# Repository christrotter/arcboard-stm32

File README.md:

# 2025/11/25 update
Ok, we found the main problem.
The Schottky diode on the main VBUS inbound power leg (just after the main polyfuse) was the problem.  After many hours of troubleshooting, we discovered that it was the thing getting hot.
More digging revealed that it had a 1A max, and after 75C its performance tanked pretty fast.  In practice it could tolerate about 0.5A before overheating got out of hand.
I replaced it with a bodge wire and the overheating problem went away - the board is now just warm with 1.1A going through it - probably some other components are 1A-rated.  I did not anticipate drawing this much current... my bad!
As a side effect of removing the diode, VBUS detection no longer works properly, so that needs to be disabled in code.

The next iteration will be a massive overhaul, so I'm not going to fix the problem.  In theory, we need both a higher quality component, a bigger package, and higher current rating.

# 2025/11/23 update 
I've, unsurprisingly, found some flaws.
Aside from the flaws mentioned (that were fixed), there's something very wrong with the power filter circuit or power trace widths.
Everything works, but it consumes 2x the power it should be consuming, and overwhelms the power traces so that they get rather hot.  I had to reduce brightness quite a bit to keep it at 'warm' levels.  Unfortunately I don't own an infrared camera, so only have temperature sensing by feel, but the area that gets hottest is in the power filter area.  I tried using the solder pad bypass, but no difference.
So, feels like it's a trace problem...?  Or maybe a bad component?  Will update when I figure it out.
If you're only running the Cyboard pcbs, PMW, dpad/paddles, it consumes about 0.25A per side.

# stm32-inator

In the search for better performance, I moved from [RP2040](https://github.com/christrotter/mk19-rp2040) (`125mhz`) to STM32F405 (`168mhz`).  Getting familiar with STM32 also allows me more confidence to move to the H7** chips in future (`550mhz`).

`v1.0 board has been tested - works w. 2 easy bodges & code.  Issues fixed in v1.1 - won't be ordering that, so untested - minor changes, should be fine?`

Many thanks to Drashna, burkfers, GeorgeN, badjeff, and the various people (tzarc) I snaggled stuff from - as always, these projects are a community effort.

## First run production

### issues
While things work, there are some problems...
- both mosfets are incorrectly wired up (maybe bad footprint?), and frankly i don't see a need for them as we're not doing batteries; the original thought was 'full power down', dunno if that's a real need; clipping them off removes the issue, and there are sufficient workarounds
- the DFU circuit cannot tolerate the LCD being plugged in; something? in that circuit prevents the cap from charging up
  - there is something foundational here that I am not equipped to deal with atm; 'works, until 3v3 devices in play'

### discoveries
...and some 'you have to try it to know' discoveries, and secondary pcb issues...
- 8mhz crystal is not the default in QMK -> 12mhz is; can be fixed in a few lines of code, but not ideal
- turns out 10 ffc cables are pretty annoying and i'd have been better served moving to two custom ffc cables
- the ffc connectors are kinda sad to use; need to make some kind of tool? -> kinda points in the direction of hot plate if i want to be choosy about parts
- the horizontal JST-XH fit...barely... i neglected to account for 'space to slide the connector in' and so you need to trim the JST housings to avoid fouling on parts - move away from this design in future, JST-PH?

### wins
...but not all is lost:
- remote usb port works absolutely fine
- DFU circuit is super rad (when it works)
- no awful bodging required this time!
- the diode arrays work
- STM32 cpu/etc all works
- silkscreen looks good
- matrix works
- spi pmw/lcd work

### conclusion
All in all, this is a win, and it'll work for mk20.

# Features
- STM32F405RGTx w. 12mhz crystal
- 128mb external flash via SPI
  - Because I Can™ by drashna®
- FFC connections (mostly), using VIK-footprinted 12-pin 0.5mm pitch connectors
- Rough footprint is 60x60mm
- Designed for remote-mount USB and split-serial ports
- WS2812 signal conversion to 5v
- Two-stage DFU button, on-board for convenience, headers for an external button
  - Press for reset
  - Hold for ~4s to enter DFU mode for flashing
  - `NOTE: when 3v3 devices are connected, the hold-for-dfu stops working :'(`
- Designed for Arcboard-mk20 peripherals
  - 4x dpad outputs (5rows, 1col, LED DI/DO, 5v/gnd)
  - 3x encoders outputs (encoder A/B, 3.3v/gnd)
  - 1x SPI PMW output (usual pins)
  - 1x SPI LCD output (usual pins)
  - 1x 25-pin Cyboard connector (0.3mm FPC connector for [Cyboard](https://www.cyboard.digital/product-page/dactyl-flex-pcbs) connectivity (or via [this](https://github.com/christrotter/mk19-flex-pcb)))
- 2-layer design for simplicity and cost

# Design notes & decisions
## CPU
I had originally wanted to go whole-hog and start with STM32H723 (as mentioned, 550mhz), but there are a lot of Chibios/QMK config bits to set that are not well-documented at present.  As 550mhz is super overkill for a keyboard, it's not a widely used chip - so examples are sparse or non-existent.

Drashna recommended starting with F405 and so who am I to second-guess them.

## Flash
At present (August 2025) QMK cannot support external flash for code execution, but feature work is on-going.  I was advised by Drashna to include the flash chip for future-proofing.  My hope is to use it for icon storage and the like.

Why 128mb?  Because it was a few bucks difference compared to 16mb, and there was no real (evident) reason not to.

## Remote-mount USB/split-serial port
This is mostly a mk20 design thing - I wanted to have the split-serial connector be at an angle, not coming off the back of the board.  When the ports are in the back, it's awkward to figure out which one is main, which one is split.  Drashna pointed out that he's been using [these](https://www.aliexpress.com/item/1005005997783735.html) which have 12cm cables and has no USB issues at all.  After a hiccup with JLC PCBA design review, I had to cancel the order and re-submit, and took the plunge...there was no room for both an on-board port and breakout pins.

  - JLC PCBA charges ~C$6 per usb port (per board...), and I've had soldering issues w. those components before
  - No more fuss with v-cut layer drama and them wanting me to use EasyEDA
  - I don't have a USB-C source, and I'm not selling this, so...whatever...
  - note that the remote-port needs to have 5.1k pull-down resistors on the CC lines to function on a USB-C host port

## Device/peripheral connectivity
I explicitly wanted to move away from JST-XH (or any soldered connector) because of pain issues doing all that soldering.  This board's goal was 'minimize soldering, maximize PCBA-ing'.

Given that I like the [VIK standard](https://github.com/sadekbaroudi/vik), I went with VIK footprints - 12-pin 0.5mm pitch FFC.  Not all of the pinouts are VIK-correct, but at least it keeps things somewhat standardized.

## Breakouts
To save space while also future-proofing, I was advised to include breakouts (thx GeorgeN/burkfers).

- Main USB & Split/serial via 2.54mm 4-pin header (I left room for a horizontal JST-XH socket)
- RGB data output via 2.54mm 3-pin header
- Reset, boot pins via 1.00mm 4-pin header
- 5 spare pins via 1.00mm 2-pin and 3-pin headers
- Debug pins via 1.00mm 4-pin header

## Spare pins
The 5 spare pins were initially going to be used for the matrix, but I cut out some features (RKJXT) and didn't need them.  They are available via headers.

Suggestions I've had:
- audio
- haptic

## Solder pads
There are a number of 'config' settings you can achieve using solder pads.  I had originally thought about using DIP switches or something...but burkfers counseled me to just stick with solder pads.

- Set [handedness](https://docs.qmk.fm/features/split_keyboard#handedness-by-pin)
- Bypass VBUS power safeties (I keep this in because I don't know what a fuse failure would look like)
- "turn on" power to the RGB and LCD mosfets

## PCB design
I decided to stick with a 2-layer stackup because I was already comfortable with using pours and vias to keep the ground plane consistent.  We'll see if that pans out.

It's important to note that if you don't provide for good ground pathing 2-layers is a bad choice.  It's "easier" to do a 4-layer board in that regard.

When ordering, I used the 'rails by JLC' option.

## Dimensions
[The RP2040 board](https://github.com/christrotter/mk19-rp2040) was `~125x75mm`, and burkfers challenged me to make this one more compact.  So a few design iterations in and we got `~60x60mm`... which unfortunately got mangled to `59.5x59.7mm`.  I'm still learning pcb design, and Kicad doesn't make it easy (or I have yet to learn the method) to keep things oriented/placed relative to center.

- 51.55mm hole spacing (square)
- M3 holes
- 59.5x59.7mm actual board size

## Matrix arrangement
I moved away from the SPI register design not because it was broken, but because you are effectively artificially limiting 'speed' with the SPI bus (sort of?).  I'm using `ROW2COL` because the Cyboard pcb's are designed this way.  

I decided to try diode "arrays" ([BAV70S - High-speed switching double diode](https://jlcpcb.com/partdetail/Nexperia-BAV70S115/C455031)) this time to save space.  However, this came with some fairly dramatic trace routing challenges.

- 6 rows
- 10 columns

## QMK
I mention `ROW2COL` and QMK not because ZMK or other won't work, but because it's what I am familiar with.

This board is intended to control half of a split keyboard, so you need two.

# Links
- [Datasheet for STM32F405](https://www.st.com/resource/en/datasheet/dm00037051.pdf)
- [Great article on STM32 DFU circuit](https://acheronproject.com/reset_article_1/reset_article_1/)
- [Great article on USB-C CC lines](https://hackaday.com/2023/01/04/all-about-usb-c-resistors-and-emarkers/)
- [TI pdf on USB-C power](https://www.ti.com/lit/wp/slyy109b/slyy109b.pdf)
- [USB and Type-C demystified](https://www.st.com/content/dam/AME/2019/technology-tour-2019/chicago/presentations/T1S3_Schaumburg_USB-Type-C_G.Gosciniak.pdf)
- [SPI flash on STM32](https://mischianti.org/stm32-add-spi-flash-memory-with-fat-fs/)

# BOM (v1.1)
|Designator                                  |Footprint                              |Quantity|Value               |LCSC Part #|
|--------------------------------------------|---------------------------------------|--------|--------------------|-----------|
|C1, C10, C20                                |0805                                   |3       |4.7uF               |C1779      |
|C11, C12, C14, C17, C18, C19, C5, C7, C8, C9|0402                                   |10      |100nF               |C1525      |
|C13, C15, C27                               |0402                                   |3       |1uF                 |C52923     |
|C2, C4                                      |0402                                   |2       |2.2uF               |C12530     |
|C22                                         |C0603                                  |1       |CL10A106MA8NRNC     |C96446     |
|C3, C6                                      |0402                                   |2       |12p                 |C1547      |
|CYBOARD-MAIN1                               |FPC-SMD_ECT818001569                   |1       |ECT818001569        |C711420    |
|D2                                          |D_SOD-323                              |1       |B5817               |C123899    |
|D4                                          |SOD-123FL_L2.8-W1.8-LS3.7-BI           |1       |SMF5_0CA_C364279    |C364279    |
|D5, D7                                      |SOT-666-6_L1.6-W1.2-P0.50-LS1.6-BL     |2       |USBLC6-2P6_C2827693 |C2827693   |
|F1                                          |F1206                                  |1       |Polyfuse            |C2892424   |
|F3                                          |F1206                                  |1       |MF-NSMF075-2        |C89653     |
|J13, J14, J15, J16, J3, J4, J6, J7, J8      |FFC-SMD_FFC05001-12SBA124W5M           |9       |FFC05001-12SBA124W5M|C2833760   |
|L1                                          |L0805                                  |1       |MPZ2012S101AT000    |C15957     |
|LED-LVL1                                    |SOT-563_L1.6-W1.2-P0.50-LS1.6-BR       |1       |SN74LVC1T45DRL      |C352970    |
|MOSFET1, MOSFET2, MOSFET3                   |SOT-23_L2.9-W1.3-P1.90-LS2.4-BR        |3       |AO3401A             |C15127     |
|R1                                          |0402                                   |1       |0402WGF1004TCE      |C26083     |
|R10                                         |0402                                   |1       |5.1k                |C25905     |
|R11, R12, R16, R2, R3, R7, R8               |0402                                   |7       |10k                 |C25744     |
|R14                                         |0402                                   |1       |0402WGF1000TCE      |C25076     |
|R15                                         |0402                                   |1       |0402WGF1001TCE      |C11702     |
|R6                                          |R0603                                  |1       |0603WAF3303T5E      |C23137     |
|R9                                          |0402                                   |1       |0402WGF1003TCE      |C25741     |
|U1                                          |SOT-23-5                               |1       |XC6210B332MR-G      |C82942     |
|U10                                         |SOD-123F_L2.7-W1.6-LS3.8-RD            |1       |1N4148W_C81598      |C81598     |
|U13, U4                                     |SOT-23-3_L2.9-W1.3-P1.90-LS2.4-BR      |2       |2N7002              |C8545      |
|U14                                         |SOIC-8_L5.3-W5.3-P1.27-LS8.0-BL        |1       |W25Q128JVSIQTR      |C97521     |
|U15                                         |SW-SMD_4P-L5.1-W5.1-P3.70-LS6.5-TL_H1.5|1       |TS-1187A-B-A-B      |C318884    |
|U3                                          |LQFP-64_10x10mm_P0.5mm                 |1       |STM32F405RGTx       |C15742     |
|U5, U6, U7, U8, U9                          |SOT-363-6_L2.0-W1.3-P0.65-LS2.1-BL     |5       |BAV70S,115          |C455031    |
|Y1                                          |CRYSTAL-SMD_4P-L3.2-W2.5-BL-1          |1       |Crystal_GND24       |C9002      |

# Layout

# PCB overview

# Schematic
`NOTE: I didn't update the screenshots, sorry.  See the kicad files for the fixed mosfets.`

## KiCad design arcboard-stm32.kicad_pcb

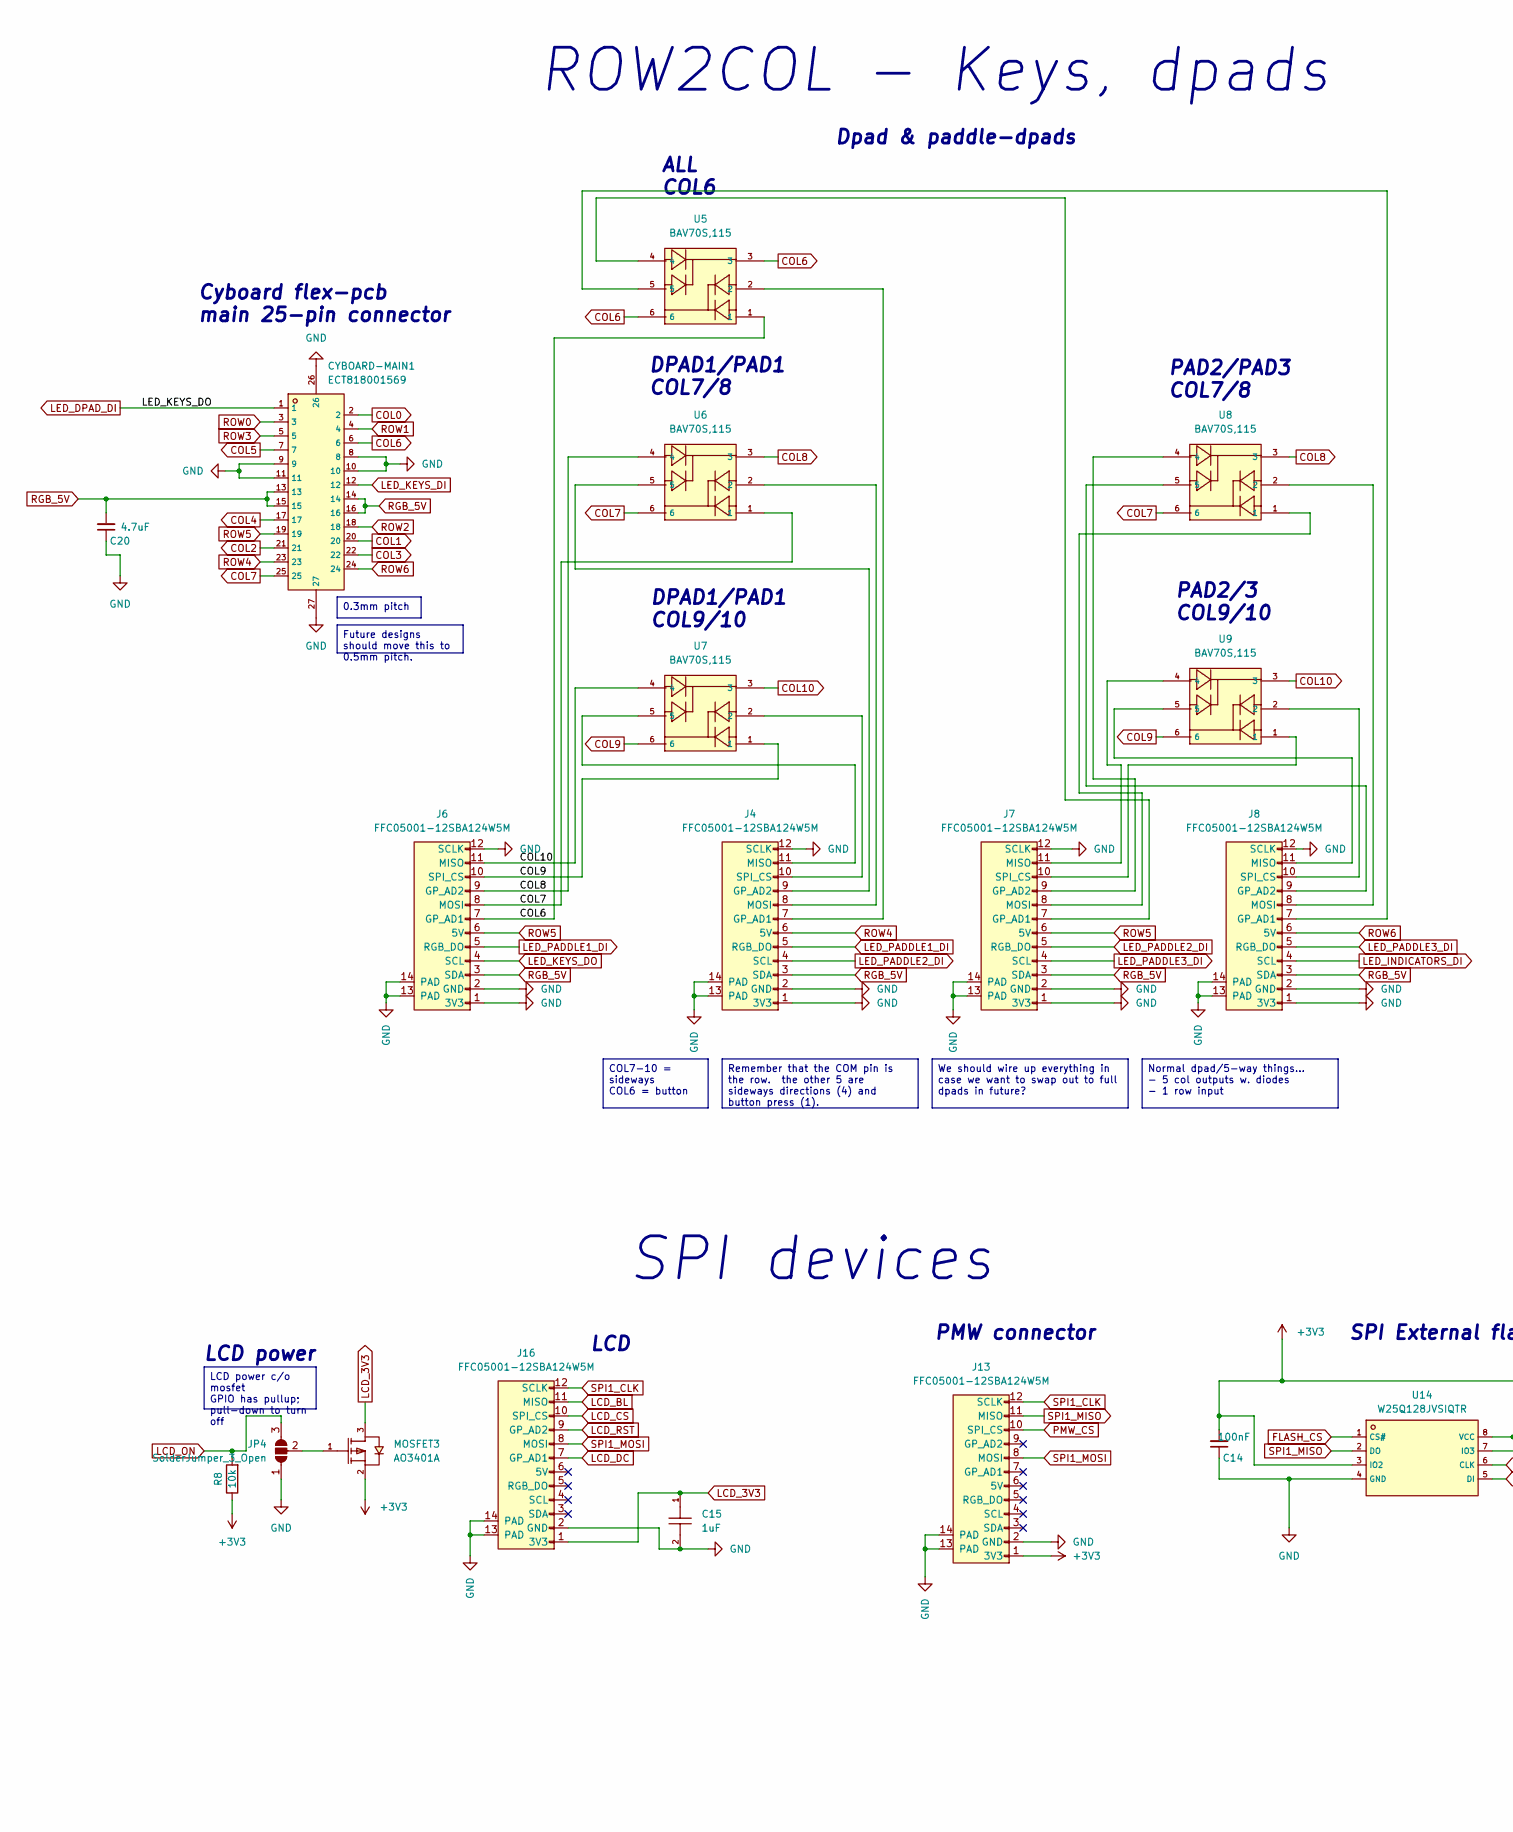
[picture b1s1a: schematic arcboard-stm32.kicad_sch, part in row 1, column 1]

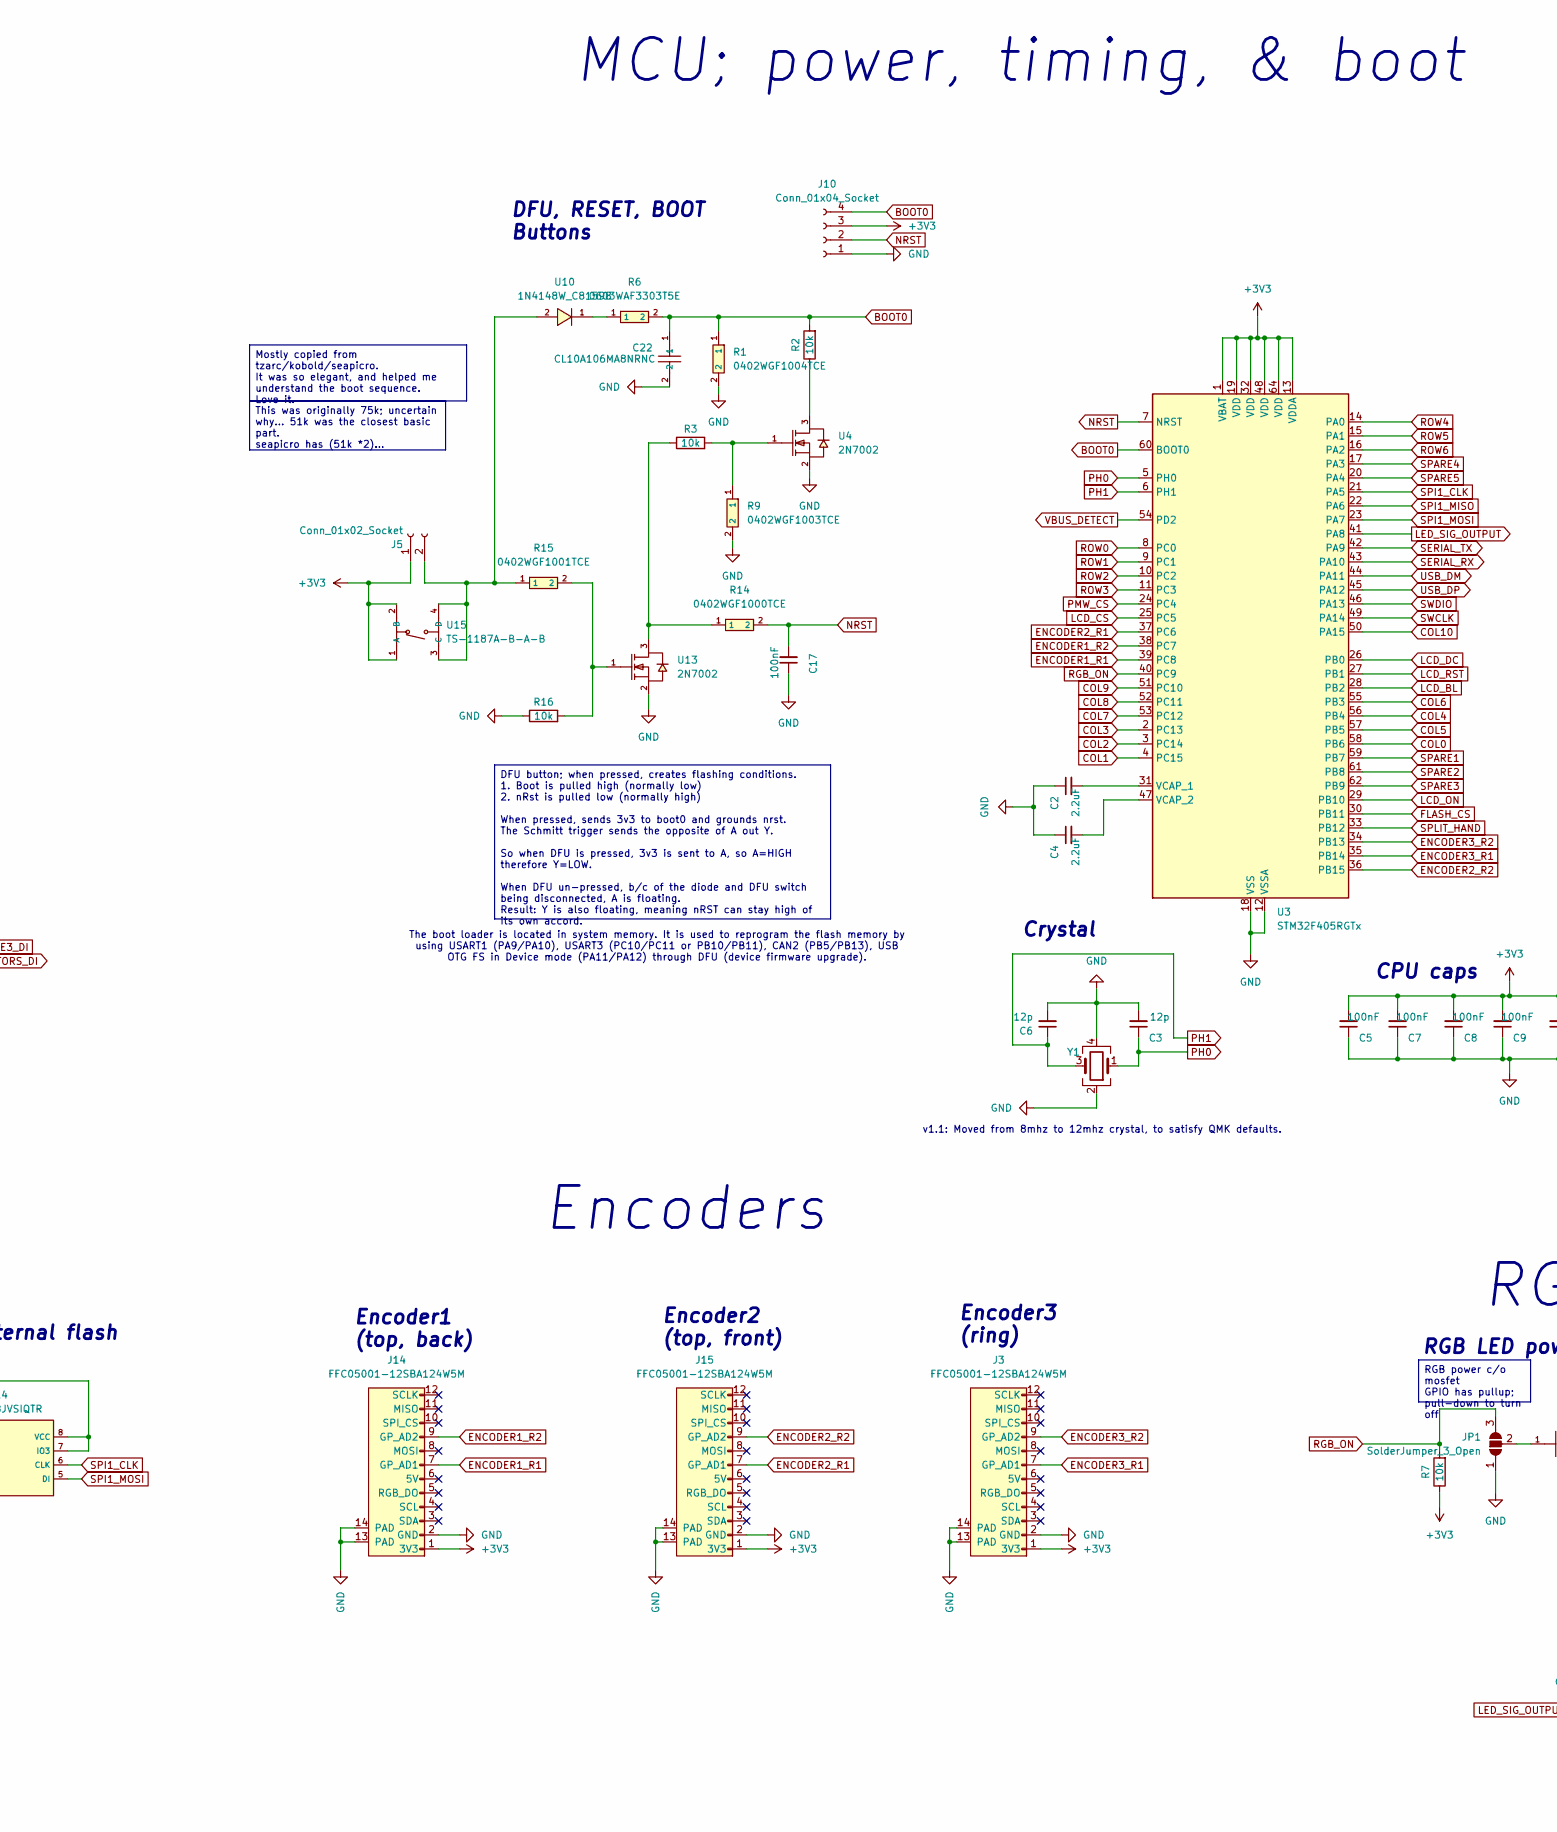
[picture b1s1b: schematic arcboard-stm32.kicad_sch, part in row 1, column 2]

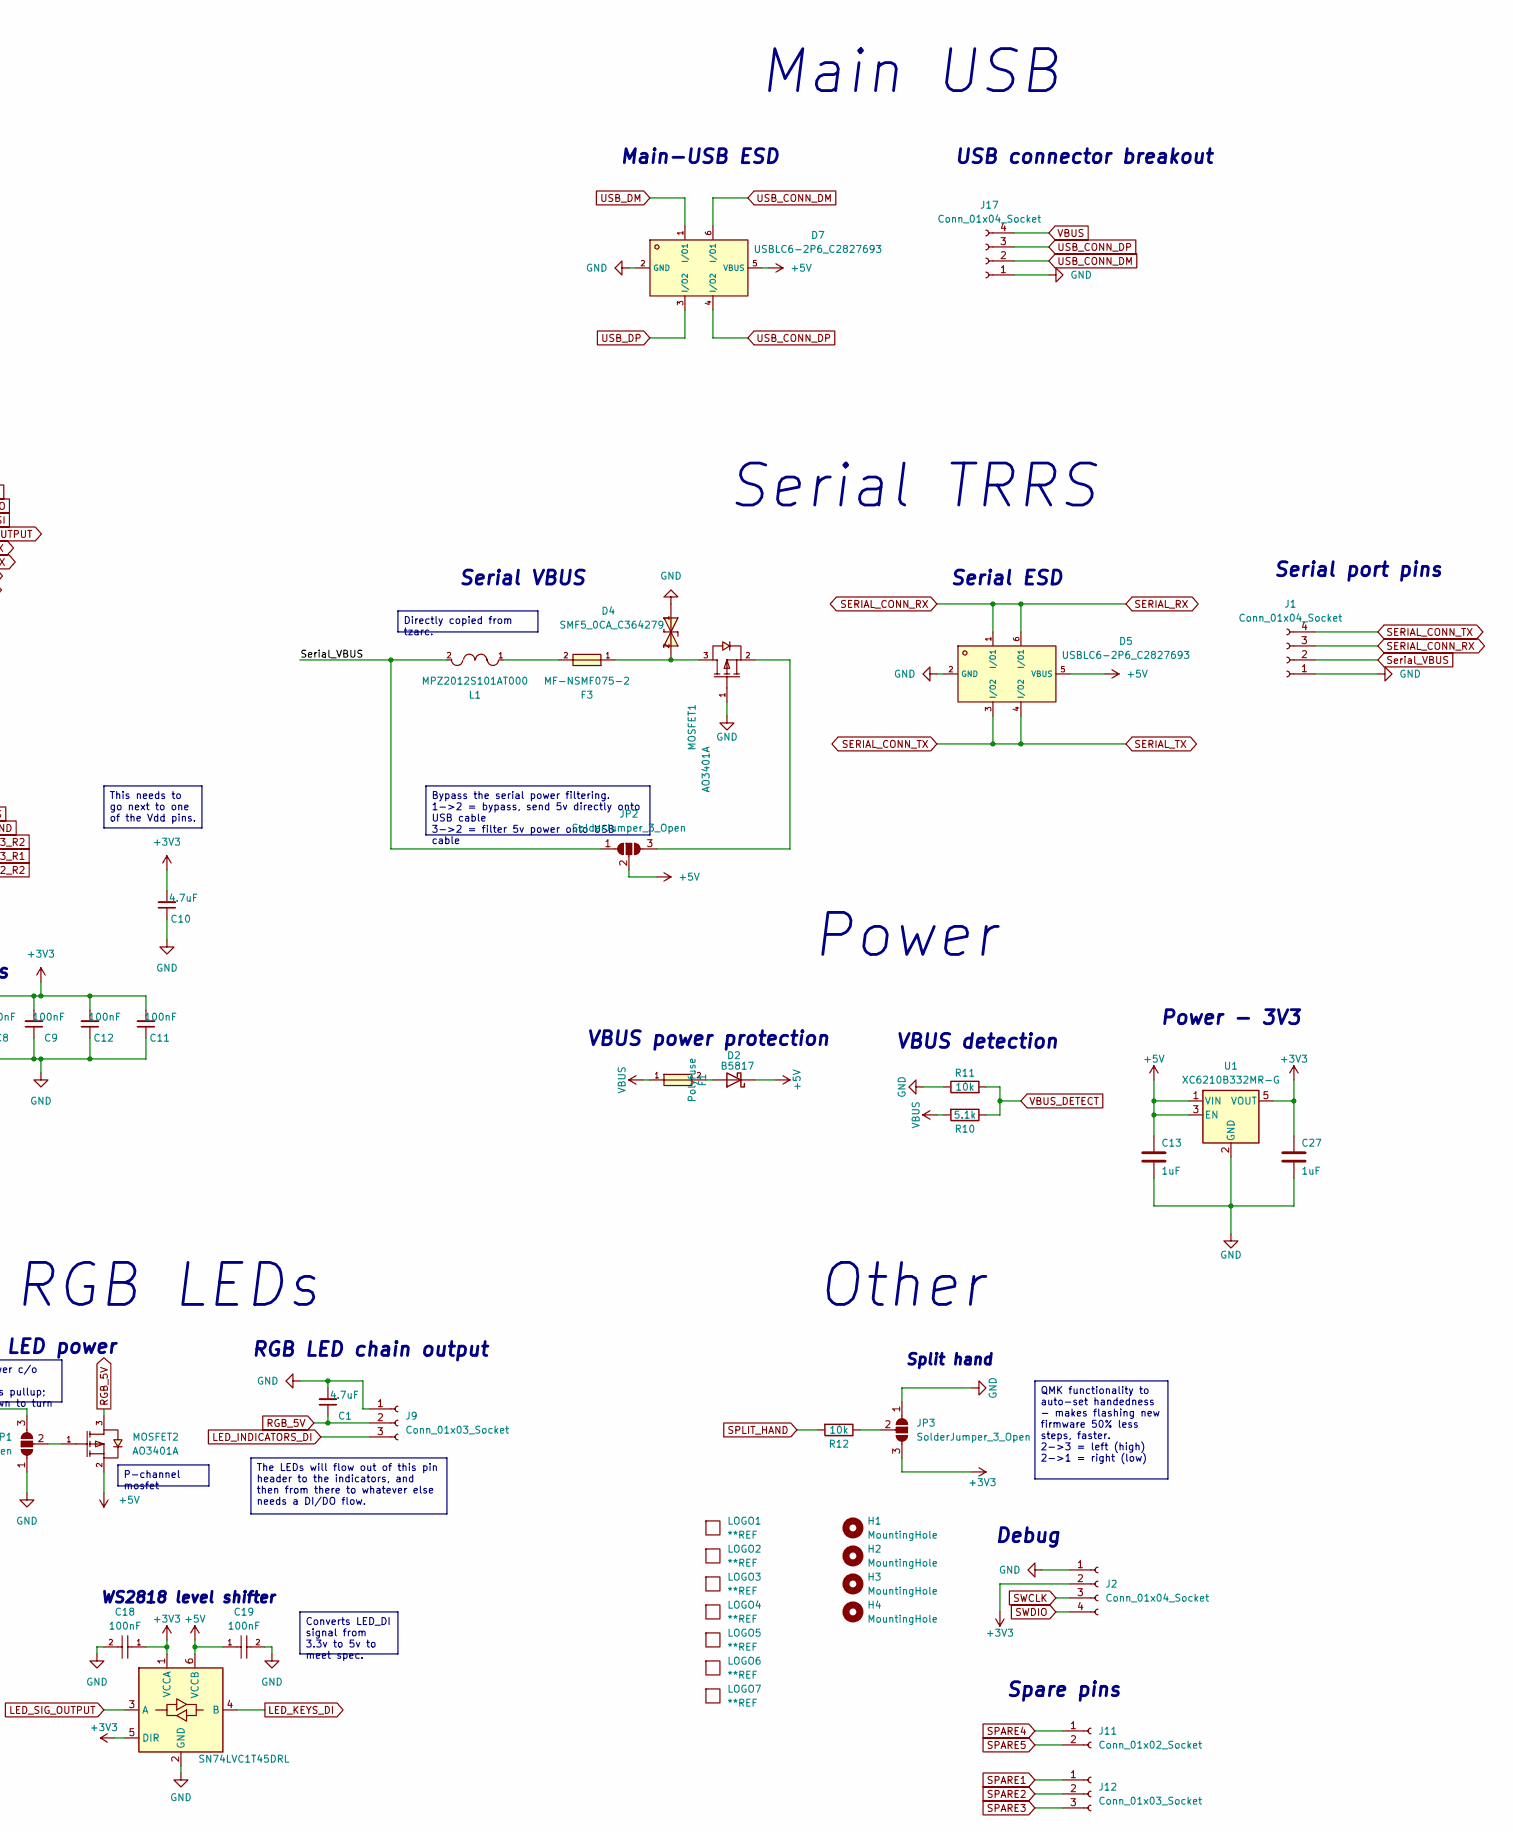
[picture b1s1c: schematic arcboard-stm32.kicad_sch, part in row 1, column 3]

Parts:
C1, C10, C20: 4.7uF; C_0805_2012Metric; LCSC C1779
C2, C4: 2.2uF; C_0402_1005Metric; LCSC C12530
C3, C6: 12p; C_0402_1005Metric; LCSC C1547
C5, C7, C8, C9, C11, C12, C14, C17, C18, C19: 100nF; C_0402_1005Metric; LCSC C1525
C13, C15, C27: 1uF; C_0402_1005Metric; LCSC C52923
C22: CL10A106MA8NRNC; C0603; LCSC C96446
CYBOARD-MAIN1: ECT818001569; FPC-SMD_ECT818001569; LCSC C711420
D2: B5817; D_SOD-323; LCSC C123899
D4: SMF5_0CA_C364279; SOD-123FL_L2.8-W1.8-LS3.7-BI; LCSC C364279
D5, D7: USBLC6-2P6_C2827693; SOT-666-6_L1.6-W1.2-P0.50-LS1.6-BL; LCSC C2827693
F1: Polyfuse; F1206; LCSC C2892424
F3: MF-NSMF075-2; F1206; LCSC C89653
H1, H2, H3, H4: MountingHole; MountingHole_3.2mm_M3_Pad_Via
J1: Conn_01x04_Socket; PinHeader_1x04_P2.54mm_Vertical
J2: Conn_01x04_Socket; PinSocket_1x04_P1.00mm_Vertical
J3, J4, J6, J7, J8, J13, J14, J15, J16: FFC05001-12SBA124W5M; FFC-SMD_FFC05001-12SBA124W5M; LCSC C2833760
J5: Conn_01x02_Socket; PinSocket_1x02_P2.54mm_Vertical
J9: Conn_01x03_Socket; PinHeader_1x03_P2.54mm_Vertical
J10: Conn_01x04_Socket; PinHeader_1x04_P1.00mm_Vertical
J11: Conn_01x02_Socket; PinHeader_1x02_P1.00mm_Vertical
J12: Conn_01x03_Socket; PinHeader_1x03_P1.00mm_Vertical
J17: Conn_01x04_Socket; JST_XH_S4B-XH-A_1x04_P2.50mm_Horizontal
JP1, JP4: SolderJumper_3_Open; SolderJumper-3_P1.3mm_Open_RoundedPad1.0x1.5mm
JP2, JP3: SolderJumper_3_Open; SolderJumper-3_P1.3mm_Open_Pad1.0x1.5mm
L1: MPZ2012S101AT000; L0805; LCSC C15957
LED-LVL1: SN74LVC1T45DRL; SOT-563_L1.6-W1.2-P0.50-LS1.6-BR; MPN SN74LVC1T45DRLR; JLC Basic N
LOGO1, LOGO2: **REF; awesome-logo
LOGO3: **REF; cyboard-logo-10mm
LOGO4: **REF; qmk-lite
LOGO5: **REF; arcboard-stm32-qr-code-10x10
LOGO6: **REF; cyboard-logo-5mm
LOGO7: **REF; awesome-logo-25mm
MOSFET1, MOSFET2, MOSFET3: AO3401A; SOT-23_L2.9-W1.3-P1.90-LS2.4-BR; LCSC C15127
R1: 0402WGF1004TCE; R_0402_1005Metric; LCSC C26083
R2, R3, R7, R8, R11, R12, R16: 10k; R_0402_1005Metric; LCSC C25744
R6: 0603WAF3303T5E; R0603; LCSC C23137
R9: 0402WGF1003TCE; R_0402_1005Metric; LCSC C25741
R10: 5.1k; R_0402_1005Metric; LCSC C25905
R14: 0402WGF1000TCE; R_0402_1005Metric; LCSC C25076
R15: 0402WGF1001TCE; R_0402_1005Metric; LCSC C11702
U1: XC6210B332MR-G; SOT-23-5; LCSC C82942
U3: STM32F405RGTx; LQFP-64_10x10mm_P0.5mm; LCSC C15742
U4, U13: 2N7002; SOT-23-3_L2.9-W1.3-P1.90-LS2.4-BR; LCSC C8545
U5, U6, U7, U8, U9: BAV70S,115; SOT-363-6_L2.0-W1.3-P0.65-LS2.1-BL; LCSC C455031
U10: 1N4148W_C81598; SOD-123F_L2.7-W1.6-LS3.8-RD; LCSC C81598
U14: W25Q128JVSIQTR; SOIC-8_L5.3-W5.3-P1.27-LS8.0-BL; LCSC C97521
U15: TS-1187A-B-A-B; SW-SMD_4P-L5.1-W5.1-P3.70-LS6.5-TL_H1.5; LCSC C318884
Y1: Crystal_GND24; CRYSTAL-SMD_4P-L3.2-W2.5-BL-1; LCSC C9002

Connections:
+3V3: C5.2, C7.2, C8.2, C9.2, C10.2, C11.2, C12.2, C14.2, C18.1, C27.1, J2.2, J3.1 (3V3), J5.1, J10.3, J13.1 (3V3), J14.1 (3V3), J15.1 (3V3), JP3.3 (B), LED-LVL1.1 (VCCA), LED-LVL1.5 (DIR), MOSFET3.2 (S), R7.1, R8.1, U1.5 (VOUT), U3.1 (VBAT), U3.13 (VDDA), U3.19 (VDD), U3.32 (VDD), U3.48 (VDD), U3.64 (VDD), U14.3 (IO2), U14.7 (IO3), U14.8 (VCC), U15.1 (A), U15.2 (B)
+5V: C13.1, C19.1, D2.1 (K), D5.5 (VBUS), D7.5 (VBUS), JP2.2 (C), LED-LVL1.6 (VCCB), MOSFET2.2 (S), U1.1 (VIN), U1.3 (EN)
BOOT0: C22.1, J10.4, R1.1, R2.2, R6.2, U3.60 (BOOT0)
COL0: CYBOARD-MAIN1.2, U3.58 (PB6)
COL1: CYBOARD-MAIN1.20, U3.4 (PC15)
COL2: CYBOARD-MAIN1.21, U3.3 (PC14)
COL3: CYBOARD-MAIN1.22, U3.2 (PC13)
COL4: CYBOARD-MAIN1.17, U3.56 (PB4)
COL5: CYBOARD-MAIN1.7, U3.57 (PB5)
COL6: CYBOARD-MAIN1.6, J6.7 (GP_AD1), U3.55 (PB3), U5.1, U5.3, U5.6
COL7: CYBOARD-MAIN1.25, J6.8 (MOSI), U3.53 (PC12), U6.1, U6.6, U8.6
COL8: J6.9 (GP_AD2), U3.52 (PC11), U6.3, U6.4, U8.3
COL9: J6.10 (SPI_CS), U3.51 (PC10), U7.1, U7.6, U9.6
COL10: J6.11 (MISO), U3.50 (PA15), U7.3, U7.4, U9.3
ENCODER1_R1: J14.7 (GP_AD1), U3.39 (PC8)
ENCODER1_R2: J14.9 (GP_AD2), U3.38 (PC7)
ENCODER2_R1: J15.7 (GP_AD1), U3.37 (PC6)
ENCODER2_R2: J15.9 (GP_AD2), U3.36 (PB15)
ENCODER3_R1: J3.7 (GP_AD1), U3.35 (PB14)
ENCODER3_R2: J3.9 (GP_AD2), U3.34 (PB13)
FLASH_CS: U3.30 (PB11), U14.1 (CS#)
GND: C1.2, C2.1, C3.2, C4.1, C5.1, C6.2, C7.1, C8.1, C9.1, C10.1, C11.1, C12.1, C13.2, C14.1, C15.2, C17.1, C18.2, C19.2, C20.1, C22.2, C27.2, CYBOARD-MAIN1.8, CYBOARD-MAIN1.9, CYBOARD-MAIN1.10, CYBOARD-MAIN1.11, CYBOARD-MAIN1.26, CYBOARD-MAIN1.27, D4.1 (K), D5.2 (GND), D7.2 (GND), J1.1, J2.1, J3.2 (GND), J3.13 (PAD), J3.14 (PAD), J4.1 (3V3), J4.2 (GND), J4.12 (SCLK), J4.13 (PAD), J4.14 (PAD), J6.1 (3V3), J6.2 (GND), J6.12 (SCLK), J6.13 (PAD), J6.14 (PAD), J7.1 (3V3), J7.2 (GND), J7.12 (SCLK), J7.13 (PAD), J7.14 (PAD), J8.1 (3V3), J8.2 (GND), J8.12 (SCLK), J8.13 (PAD), J8.14 (PAD), J9.1, J10.1, J13.2 (GND), J13.13 (PAD), J13.14 (PAD), J14.2 (GND), J14.13 (PAD), J14.14 (PAD), J15.2 (GND), J15.13 (PAD), J15.14 (PAD), J16.2 (GND), J16.13 (PAD), J16.14 (PAD), J17.1, JP1.1 (A), JP3.1 (A), JP4.1 (A), LED-LVL1.2 (GND), MOSFET1.1 (G), R1.2, R9.2, R11.1, R16.1, U1.2 (GND), U3.12 (VSSA), U3.18 (VSS), U3.63 (VSS), U4.2 (S), U13.2 (S), U14.4 (GND), Y1.2, Y1.4
LCD_3V3: C15.1, J16.1 (3V3), MOSFET3.3 (D)
LCD_BL: J16.11 (MISO), U3.28 (PB2)
LCD_CS: J16.10 (SPI_CS), U3.25 (PC5)
LCD_DC: J16.7 (GP_AD1), U3.26 (PB0)
LCD_ON: JP4.3 (B), R8.2, U3.29 (PB10)
LCD_RST: J16.9 (GP_AD2), U3.27 (PB1)
LED_DPAD_DI: CYBOARD-MAIN1.1, J6.4 (SCL)
LED_INDICATORS_DI: J8.4 (SCL), J9.3
LED_KEYS_DI: CYBOARD-MAIN1.12, LED-LVL1.4 (B)
LED_PADDLE1_DI: J4.5 (RGB_DO), J6.5 (RGB_DO)
LED_PADDLE2_DI: J4.4 (SCL), J7.5 (RGB_DO)
LED_PADDLE3_DI: J7.4 (SCL), J8.5 (RGB_DO)
LED_SIG_OUTPUT: LED-LVL1.3 (A), U3.41 (PA8)
NRST: C17.2, J10.2, R14.2, U3.7 (NRST)
unnamed: D2.2 (A), F1.2
unnamed: D4.2 (A), F3.1, MOSFET1.3 (D)
unnamed: F3.2, L1.1
unnamed: J4.7 (GP_AD1), U5.2
unnamed: J4.9 (GP_AD2), U6.5
unnamed: J4.11 (MISO), U7.5
unnamed: J4.8 (MOSI), U6.2
unnamed: J4.10 (SPI_CS), U7.2
unnamed: J5.2, R15.1, U10.2 (A), U15.3 (C), U15.4 (D)
unnamed: J7.7 (GP_AD1), U5.4
unnamed: J7.9 (GP_AD2), U8.4
unnamed: J7.11 (MISO), U9.4
unnamed: J7.8 (MOSI), U8.1
unnamed: J7.10 (SPI_CS), U9.1
unnamed: J8.7 (GP_AD1), U5.5
unnamed: J8.9 (GP_AD2), U8.5
unnamed: J8.11 (MISO), U9.5
unnamed: J8.8 (MOSI), U8.2
unnamed: J8.10 (SPI_CS), U9.2
unnamed: JP1.2 (C), MOSFET2.1 (G)
unnamed: JP2.3 (B), MOSFET1.2 (S)
unnamed: JP3.2 (C), R12.1
unnamed: JP4.2 (C), MOSFET3.1 (G)
unnamed: C2.2, U3.31 (VCAP_1)
unnamed: C4.2, U3.47 (VCAP_2)
unnamed: R2.1, U4.3 (D)
unnamed: R3.2, R9.1, U4.1 (G)
unnamed: R6.1, U10.1 (K)
unnamed: R3.1, R14.1, U13.3 (D)
unnamed: R15.2, R16.2, U13.1 (G)
PH0: C3.1, U3.5 (PH0), Y1.1
PH1: C6.1, U3.6 (PH1), Y1.3
PMW_CS: J13.10 (SPI_CS), U3.24 (PC4)
RGB_5V: C1.1, C20.2, CYBOARD-MAIN1.13, CYBOARD-MAIN1.14, CYBOARD-MAIN1.15, CYBOARD-MAIN1.16, J4.3 (SDA), J6.3 (SDA), J7.3 (SDA), J8.3 (SDA), J9.2, MOSFET2.3 (D)
RGB_ON: JP1.3 (B), R7.2, U3.40 (PC9)
ROW0: CYBOARD-MAIN1.3, U3.8 (PC0)
ROW1: CYBOARD-MAIN1.4, U3.9 (PC1)
ROW2: CYBOARD-MAIN1.18, U3.10 (PC2)
ROW3: CYBOARD-MAIN1.5, U3.11 (PC3)
ROW4: CYBOARD-MAIN1.23, J4.6 (5V), U3.14 (PA0)
ROW5: CYBOARD-MAIN1.19, J6.6 (5V), J7.6 (5V), U3.15 (PA1)
ROW6: CYBOARD-MAIN1.24, J8.6 (5V), U3.16 (PA2)
SERIAL_CONN_RX: D5.1 (I/O1), D5.6 (I/O1), J1.3, U3.43 (PA10)
SERIAL_CONN_TX: D5.3 (I/O2), D5.4 (I/O2), J1.4, U3.42 (PA9)
SPARE1: J12.1, U3.59 (PB7)
SPARE2: J12.2, U3.61 (PB8)
SPARE3: J12.3, U3.62 (PB9)
SPARE4: J11.1, U3.17 (PA3)
SPARE5: J11.2, U3.20 (PA4)
SPI1_CLK: J13.12 (SCLK), J16.12 (SCLK), U3.21 (PA5), U14.6 (CLK)
SPI1_MISO: J13.11 (MISO), U3.22 (PA6), U14.2 (DO)
SPI1_MOSI: J13.8 (MOSI), J16.8 (MOSI), U3.23 (PA7), U14.5 (DI)
SPLIT_HAND: R12.2, U3.33 (PB12)
SWCLK: J2.3, U3.49 (PA14)
SWDIO: J2.4, U3.46 (PA13)
Serial_VBUS: J1.2, JP2.1 (A), L1.2
USB_CONN_DM: D7.6 (I/O1), J17.2
USB_CONN_DP: D7.4 (I/O2), J17.3
USB_DM: D7.1 (I/O1), U3.44 (PA11)
USB_DP: D7.3 (I/O2), U3.45 (PA12)
VBUS: F1.1, J17.4, R10.2
VBUS_DETECT: R10.1, R11.2, U3.54 (PD2)

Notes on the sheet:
Spare pins
Serial port pins
PMW connector
Power
DFU, RESET, BOOT Buttons
Serial ESD
USB connector breakout
VBUS detection
VBUS power protection
DPAD1/PAD1 COL9/10
Main-USB ESD
RGB LEDs
Split hand
Cyboard flex-pcb main 25-pin connector
Dpad & paddle-dpads
ROW2COL - Keys, dpads
Power - 3V3
Other
DPAD1/PAD1 COL7/8
Debug
v1.1: Moved from 8mhz to 12mhz crystal, to satisfy QMK defaults.
PAD2/3 COL9/10
Encoders
WS2818 level shifter
The boot loader is located in system memory. It is used to reprogram the flash memory by using USART1 (PA9/PA10), USART3 (PC10/PC11 or PB10/PB11), CAN2 (PB5/PB13), USB OTG FS in Device mode (PA11/PA12) through DFU (device firmware upgrade).
Encoder1 (top, back)
CPU caps
MCU; power, timing, & boot
Crystal
PAD2/PAD3 COL7/8
SPI External flash
Serial TRRS
Main USB
SPI devices
Encoder3 (ring)
RGB LED chain output
RGB LED power
Serial VBUS
LCD power
Encoder2 (top, front)

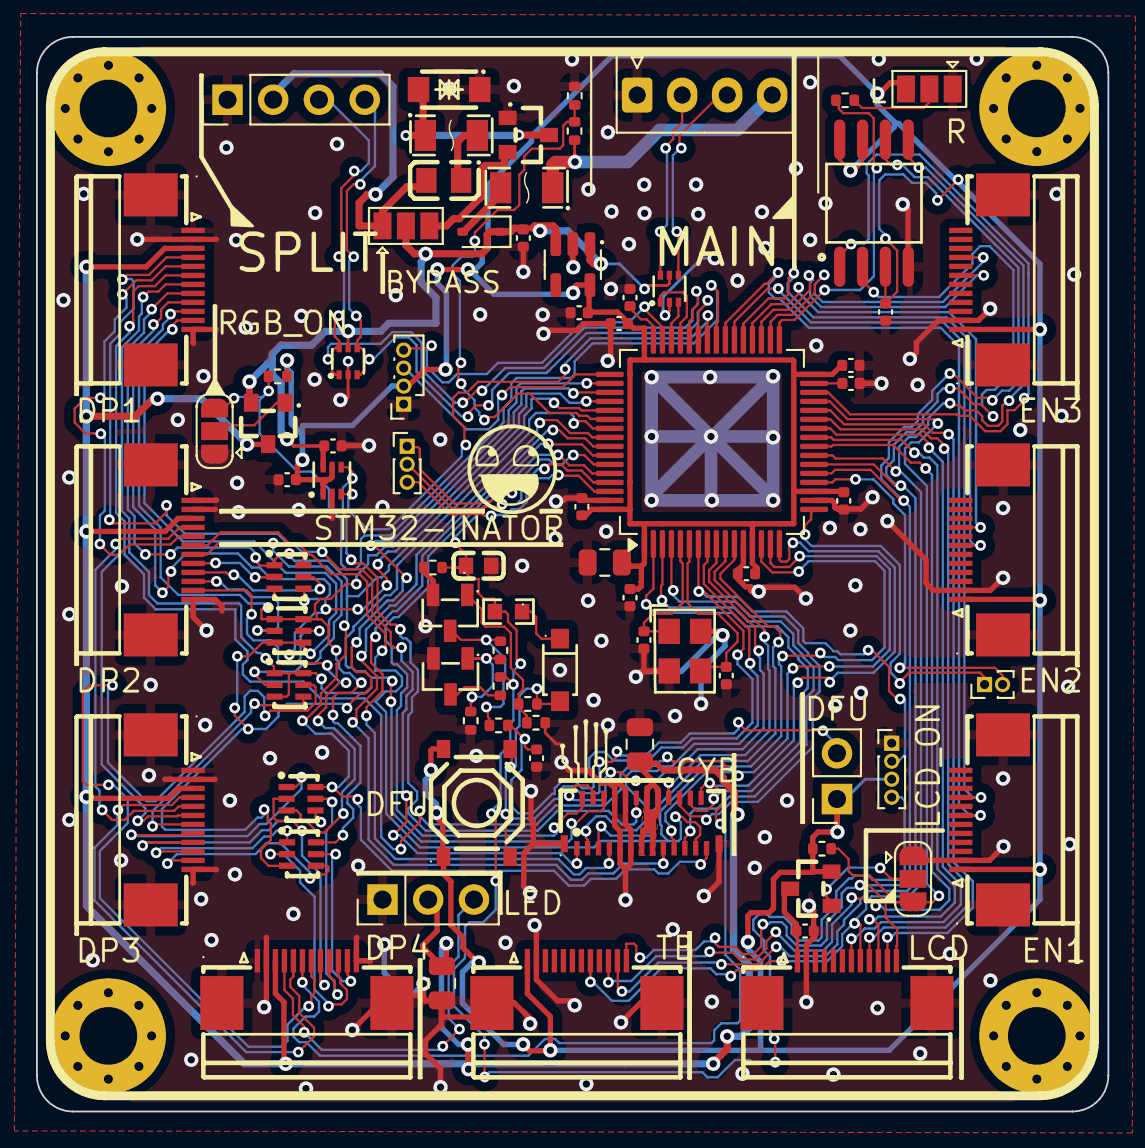
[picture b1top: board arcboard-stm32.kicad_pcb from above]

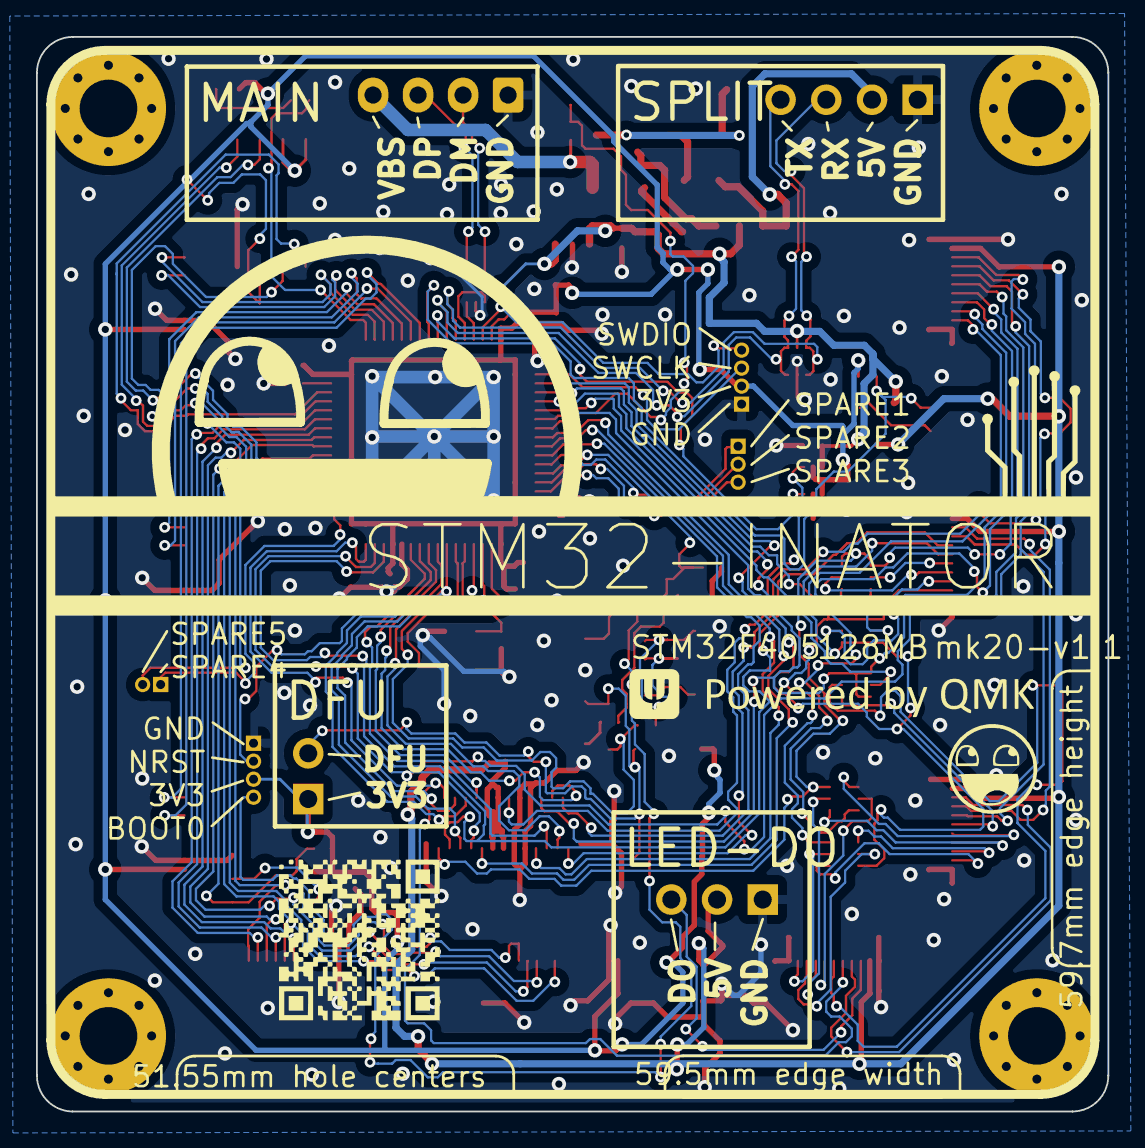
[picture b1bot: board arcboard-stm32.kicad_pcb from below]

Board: 2 copper layers, 59.5 x 59.7 mm, 91 parts (5 on the bottom side), 98 nets.

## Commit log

2025-07-21 initial commit, bare project
2025-07-24 savegame jul23
2025-07-26 mostly there
2025-07-27 savegame
2025-07-27 cleaned up routing quite a bit
2025-07-28 more trace pruning
2025-07-28 prepping for review
2025-08-15 before removal of usb port
2025-08-15 moving to separate split connector, adding flash
2025-08-15 adding spare pins, more routing
2025-08-24 silkscreen updates
2025-08-24 silkscreen improvements
2025-08-24 moved a few items, silkscreen improvements
2025-08-26 production version
2025-08-26 3d model weirdness
2025-08-26 production step file
2025-08-26 updating the readme
2025-08-26 more images, more readme
2025-08-26 enough readmeing
2025-08-27 improving readme
2025-09-07 fixing bad mosfet configuration, changing crystal to 12mhz
2025-09-07 updated readme with production run notes and pics
2025-09-07 2 not 1
